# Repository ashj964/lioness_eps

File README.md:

# lioness_eps
Design of LIONESS EPS for CSI CubeSat Mission

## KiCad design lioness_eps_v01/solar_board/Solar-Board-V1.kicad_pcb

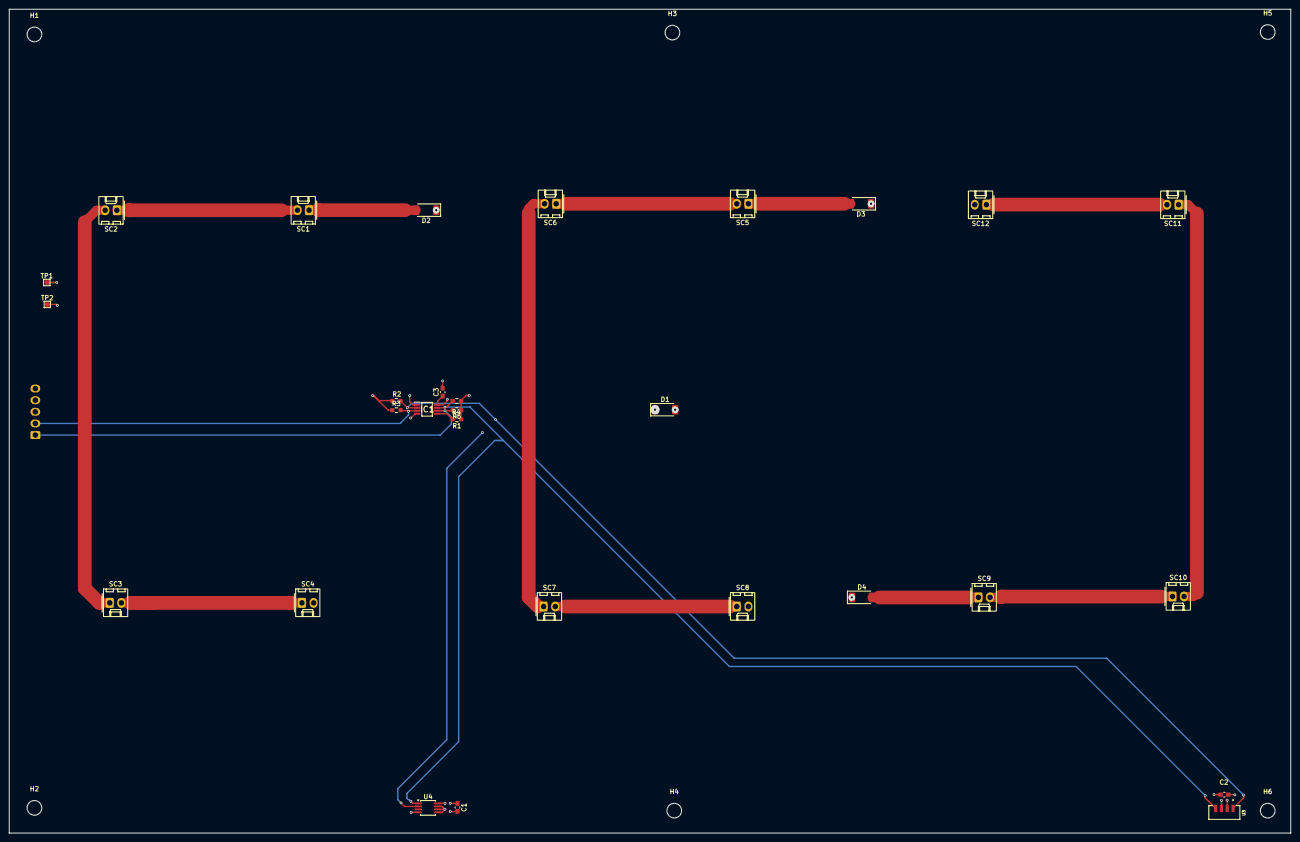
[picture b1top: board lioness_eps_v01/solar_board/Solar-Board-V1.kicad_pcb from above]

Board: 4 copper layers, 280.0 x 180.0 mm, 36 parts (1 on the bottom side), 21 nets.

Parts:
C1, C2, C3: 0.1uF; C_0603_1608Metric_Pad1.08x0.95mm_HandSolder
D1, D2, D3, D4: LEO1N5822AF; D_SOD-128
H1, H2, H3, H4, H5, H6: MountingHole; MountingHole_3.2mm_M3
IC1: TCA9511A; SOP65P490X110-8N
J1: Conn_01x05; Molex_KK-254_AE-6410-05A_1x05_P2.54mm_Vertical
R1, R2, R3, R4, R5: 10k; R_0603_1608Metric_Pad0.98x0.95mm_HandSolder
SC1, SC2, SC3, SC4, SC5, SC6, SC7, SC8, SC9, SC10, SC11, SC12: Solar_Cell; Molex_KK-254_AE-6410-02A_1x02_P2.54mm_Vertical
TP1: VSOLAR; TestPoint_Pad_1.0x1.0mm
TP2: GND; TestPoint_Pad_1.0x1.0mm
U3: VEML7700-TT; XDCR_VEML7700-TT
U4: MCP9808_MSOP; MSOP-8_3x3mm_P0.65mm

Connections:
+3.3V: C1.1, C2.1, C3.1, IC1.1 (EN), IC1.8 (VCC), J1.3, R1.1, R2.1, R3.1, R4.1, R5.1, U3.2 (VDD), U4.8 (V_{DD})
GND: C1.2, C2.2, C3.2, IC1.4 (GND), J1.4, SC4.2 (-), SC8.2 (-), SC12.2 (-), TP2.1 (1_1), U3.3 (GND), U4.4 (GND), U4.5 (A2), U4.6 (A1), U4.7 (A0)
unnamed: D1.2 (A), D2.1 (K), D3.1 (K), D4.1 (K)
unnamed: D2.2 (A), SC1.1 (+)
unnamed: D3.2 (A), SC5.1 (+)
unnamed: D4.2 (A), SC9.1 (+)
unnamed: IC1.5 (READY), R1.2
unnamed: SC1.2 (-), SC2.1 (+)
unnamed: SC2.2 (-), SC3.1 (+)
unnamed: SC3.2 (-), SC4.1 (+)
unnamed: SC5.2 (-), SC6.1 (+)
unnamed: SC6.2 (-), SC7.1 (+)
unnamed: SC7.2 (-), SC8.1 (+)
unnamed: SC9.2 (-), SC10.1 (+)
unnamed: SC10.2 (-), SC11.1 (+)
unnamed: SC11.2 (-), SC12.1 (+)
SCLIN: IC1.3 (SCLIN), J1.2, R3.2
SCLOUT: IC1.2 (SCLOUT), R2.2, U3.1 (SCL), U4.2 (SCL)
SDAIN: IC1.6 (SDAIN), J1.1, R5.2
SDAOUT: IC1.7 (SDAOUT), R4.2, U3.4 (SDA), U4.1 (SDA)
VSOLAR: D1.1 (K), J1.5, TP1.1 (1_1)

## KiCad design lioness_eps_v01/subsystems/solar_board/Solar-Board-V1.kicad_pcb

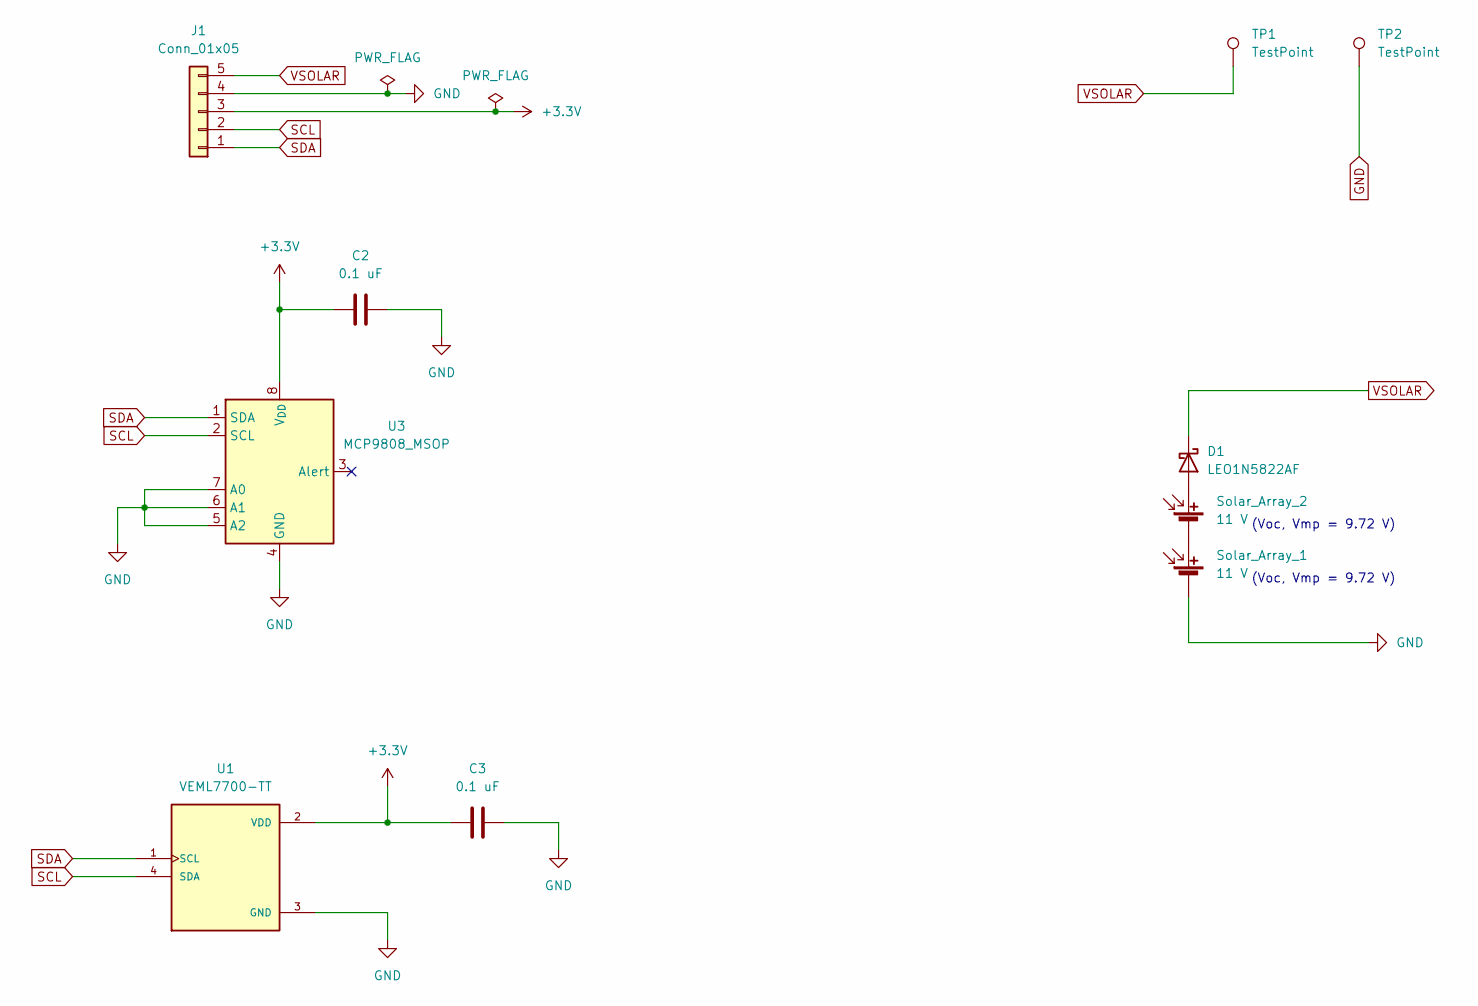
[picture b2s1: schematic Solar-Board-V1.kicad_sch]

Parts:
C2, C3: 0.1 uF; C_0603_1608Metric_Pad1.08x0.95mm_HandSolder
D1: LEO1N5822AF; D_SOD-128
J1: Conn_01x05; Molex_KK-254_AE-6410-05A_1x05_P2.54mm_Vertical
Solar_Array_1, Solar_Array_2: 11 V; Molex_KK-254_AE-6410-02A_1x02_P2.54mm_Vertical
TP1, TP2: TestPoint; TestPoint_Pad_1.0x1.0mm
U1: VEML7700-TT; XDCR_VEML7700-TT; MPN VEML7700-TT
U3: MCP9808_MSOP; MSOP-8_3x3mm_P0.65mm

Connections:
+3.3V: C2.1, C3.1, J1.3, U1.2 (VDD), U3.8 (V_{DD})
GND: C2.2, C3.2, J1.4, Solar_Array_1.2 (-), TP2.1 (1_1), U1.3 (GND), U3.4 (GND), U3.5 (A2), U3.6 (A1), U3.7 (A0)
unnamed: D1.2 (A), Solar_Array_2.1 (+)
unnamed: Solar_Array_1.1 (+), Solar_Array_2.2 (-)
SCL: J1.2, U1.4 (SDA), U3.2 (SCL)
SDA: J1.1, U1.1 (SCL), U3.1 (SDA)
VSOLAR: D1.1 (K), J1.5, TP1.1 (1_1)

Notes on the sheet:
(Voc, Vmp = 9.72 V)

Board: 2 copper layers, 10 parts (0 on the bottom side), 7 nets, no tracks yet.
